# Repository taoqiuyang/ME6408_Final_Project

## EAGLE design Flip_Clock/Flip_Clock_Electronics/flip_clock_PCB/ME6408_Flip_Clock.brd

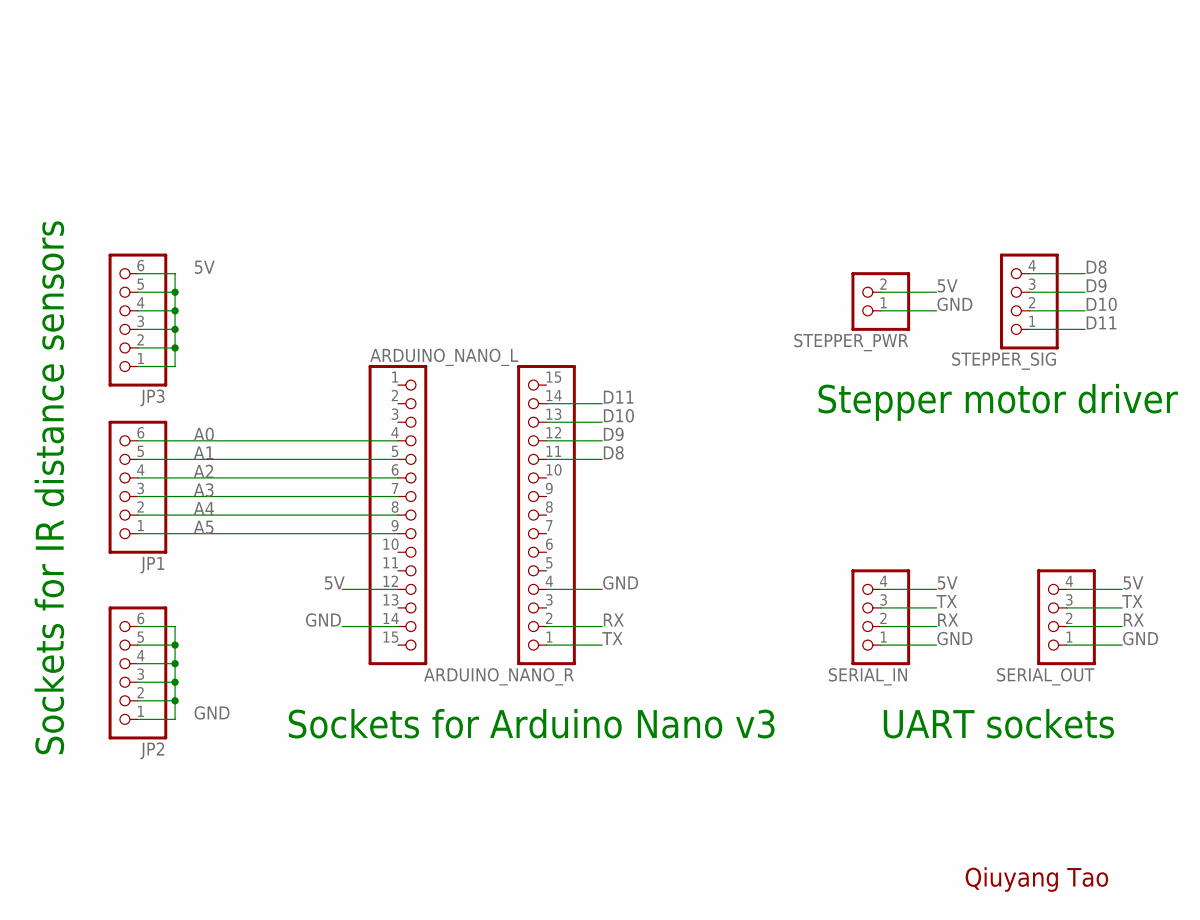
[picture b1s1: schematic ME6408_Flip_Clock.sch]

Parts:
ARDUINO_NANO_L: PINHD-1X15; 1X15
ARDUINO_NANO_R: PINHD-1X15; 1X15
JP1, JP2, JP3: PINHD-1X6; 1X06
SERIAL_IN: PINHD-1X4; 1X04
SERIAL_OUT: PINHD-1X4; 1X04
STEPPER_PWR: PINHD-1X2; 1X02
STEPPER_SIG: PINHD-1X4; 1X04

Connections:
5V: ARDUINO_NANO_L.12, JP3.1, JP3.2, JP3.3, JP3.4, JP3.5, JP3.6, SERIAL_IN.4, SERIAL_OUT.4, STEPPER_PWR.2
A0: ARDUINO_NANO_L.4, JP1.6
A1: ARDUINO_NANO_L.5, JP1.5
A2: ARDUINO_NANO_L.6, JP1.4
A3: ARDUINO_NANO_L.7, JP1.3
A4: ARDUINO_NANO_L.8, JP1.2
A5: ARDUINO_NANO_L.9, JP1.1
D8: ARDUINO_NANO_R.11, STEPPER_SIG.4
D9: ARDUINO_NANO_R.12, STEPPER_SIG.3
D10: ARDUINO_NANO_R.13, STEPPER_SIG.2
D11: ARDUINO_NANO_R.14, STEPPER_SIG.1
GND: ARDUINO_NANO_L.14, ARDUINO_NANO_R.4, JP2.1, JP2.2, JP2.3, JP2.4, JP2.5, JP2.6, SERIAL_IN.1, SERIAL_OUT.1, STEPPER_PWR.1
RX: ARDUINO_NANO_R.2, SERIAL_IN.2, SERIAL_OUT.2
TX: ARDUINO_NANO_R.1, SERIAL_IN.3, SERIAL_OUT.3

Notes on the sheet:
Sockets for Arduino Nano v3
Sockets for IR distance sensors
Stepper motor driver
UART sockets
Qiuyang Tao

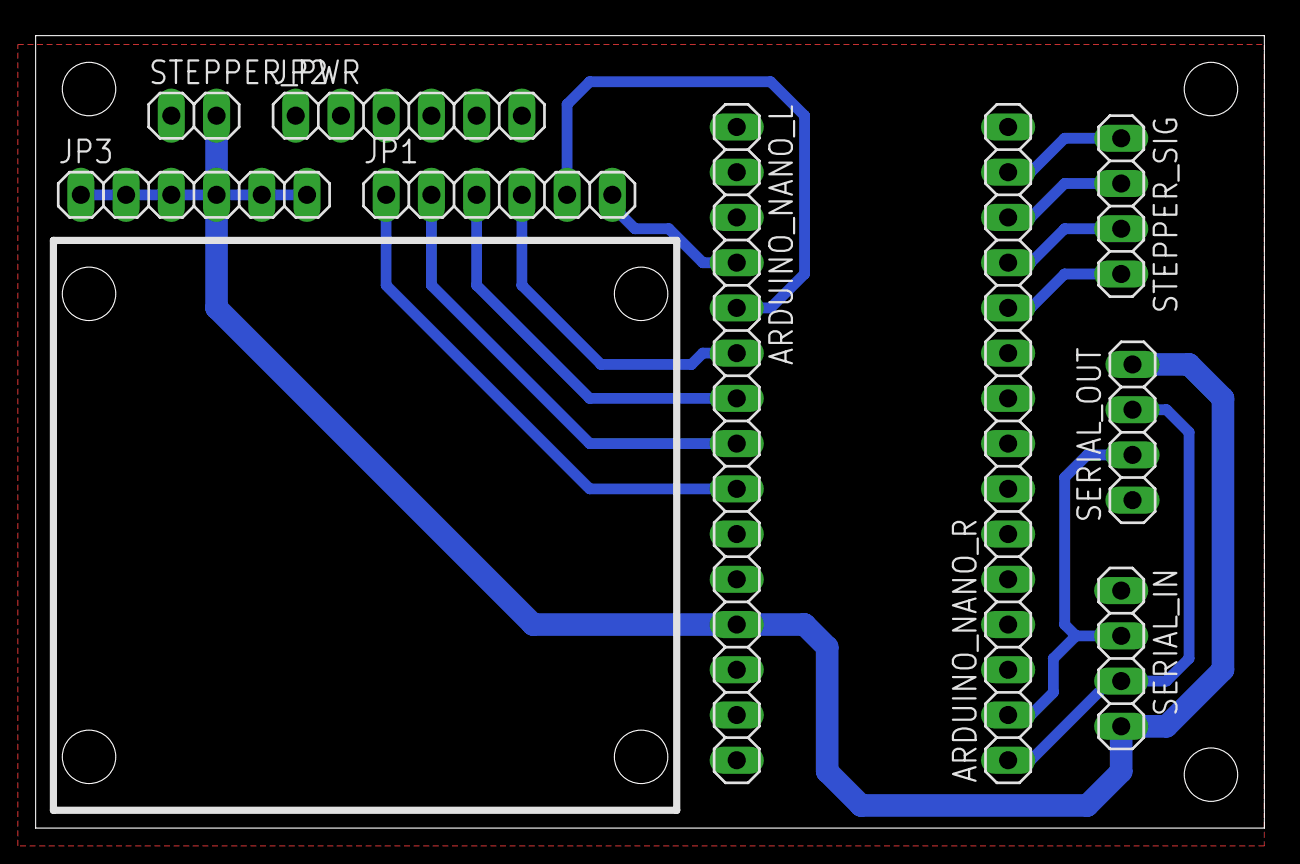
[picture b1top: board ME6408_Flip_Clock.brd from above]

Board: 2 copper layers, 69.0 x 44.5 mm, 9 parts (0 on the bottom side), 14 nets.

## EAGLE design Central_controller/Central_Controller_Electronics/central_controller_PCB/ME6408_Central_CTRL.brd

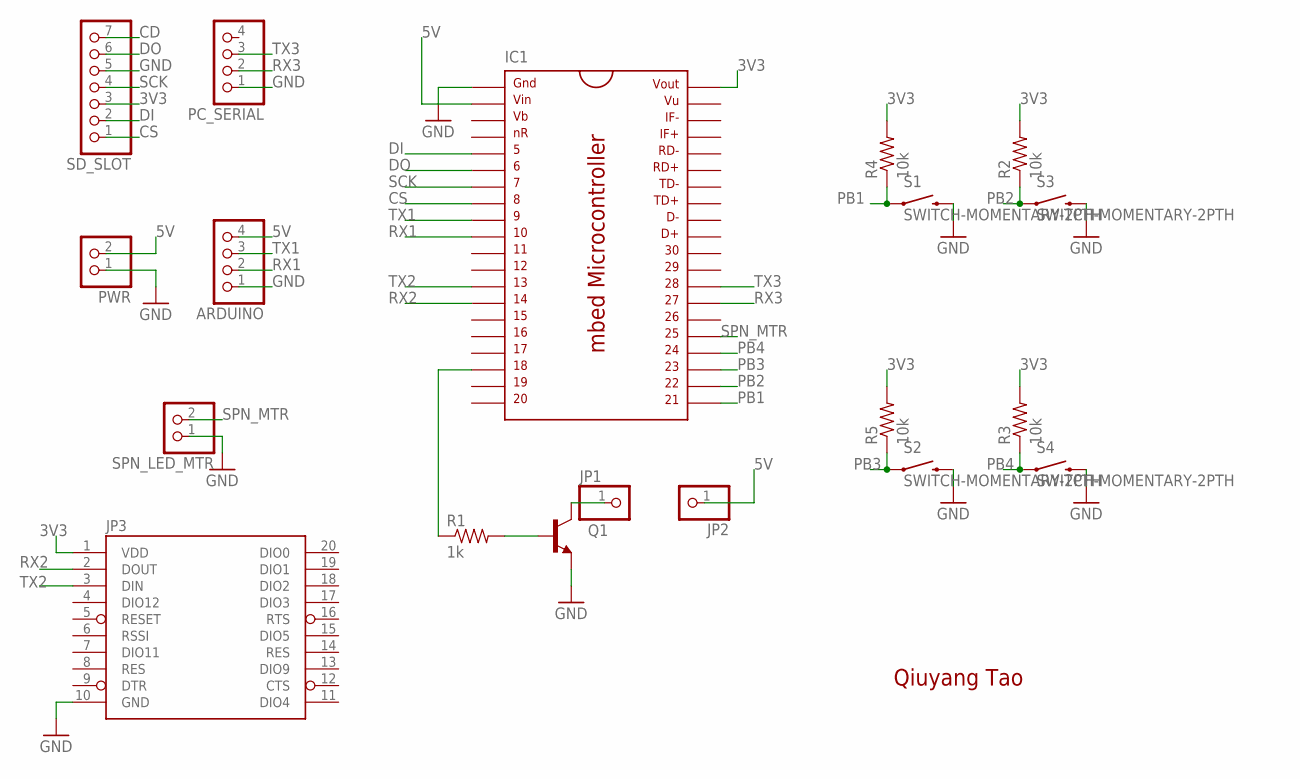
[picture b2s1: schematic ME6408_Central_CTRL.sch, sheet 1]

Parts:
ARDUINO: PINHD-1X4; 1X04
IC1: MBED_MICROCONTROLLER; DIL40_0.9
JP1, JP2: PINHD-1X1; 1X01
JP3: XBEE-1B1; XBEE-1
PC_SERIAL: PINHD-1X4; 1X04
PWR: PINHD-1X2; 1X02
Q1: TRANSISTOR_NPNTO-92-AMMO; TO-92-AMMO
R1: 1k; AXIAL-0.3
R2, R3, R4, R5: 10k; AXIAL-0.3
S1, S2, S3, S4: SWITCH-MOMENTARY-2PTH; TACTILE-PTH
SD_SLOT: PINHD-1X7; 1X07
SPN_LED_MTR: PINHD-1X2; 1X02

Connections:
3V3: IC1.40, JP3.1 (VDD), R2.P$2 (2), R3.P$2 (2), R4.P$2 (2), R5.P$2 (2), SD_SLOT.3
5V: ARDUINO.4, IC1.2, JP2.1, PWR.2
CD: SD_SLOT.7
CS: IC1.8, SD_SLOT.1
DI: IC1.5, SD_SLOT.2
DO: IC1.6, SD_SLOT.6
GND: ARDUINO.1, IC1.1, JP3.10 (GND), PC_SERIAL.1, PWR.1, Q1.1 (E), S1.3 (2), S2.3 (2), S3.3 (2), S4.3 (2), SD_SLOT.5, SPN_LED_MTR.1
unnamed: Q1.2 (B), R1.P$2 (2)
unnamed: JP1.1, Q1.3 (C)
unnamed: IC1.18, R1.P$1 (1)
PB1: IC1.21, R4.P$1 (1), S1.1
PB2: IC1.22, R2.P$1 (1), S3.1
PB3: IC1.23, R5.P$1 (1), S2.1
PB4: IC1.24, R3.P$1 (1), S4.1
RX1: ARDUINO.2, IC1.10
RX2: IC1.14, JP3.2 (DOUT)
RX3: IC1.27, PC_SERIAL.2
SCK: IC1.7, SD_SLOT.4
SPN_MTR: IC1.25, SPN_LED_MTR.2
TX1: ARDUINO.3, IC1.9
TX2: IC1.13, JP3.3 (DIN)
TX3: IC1.28, PC_SERIAL.3

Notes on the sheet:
Qiuyang Tao

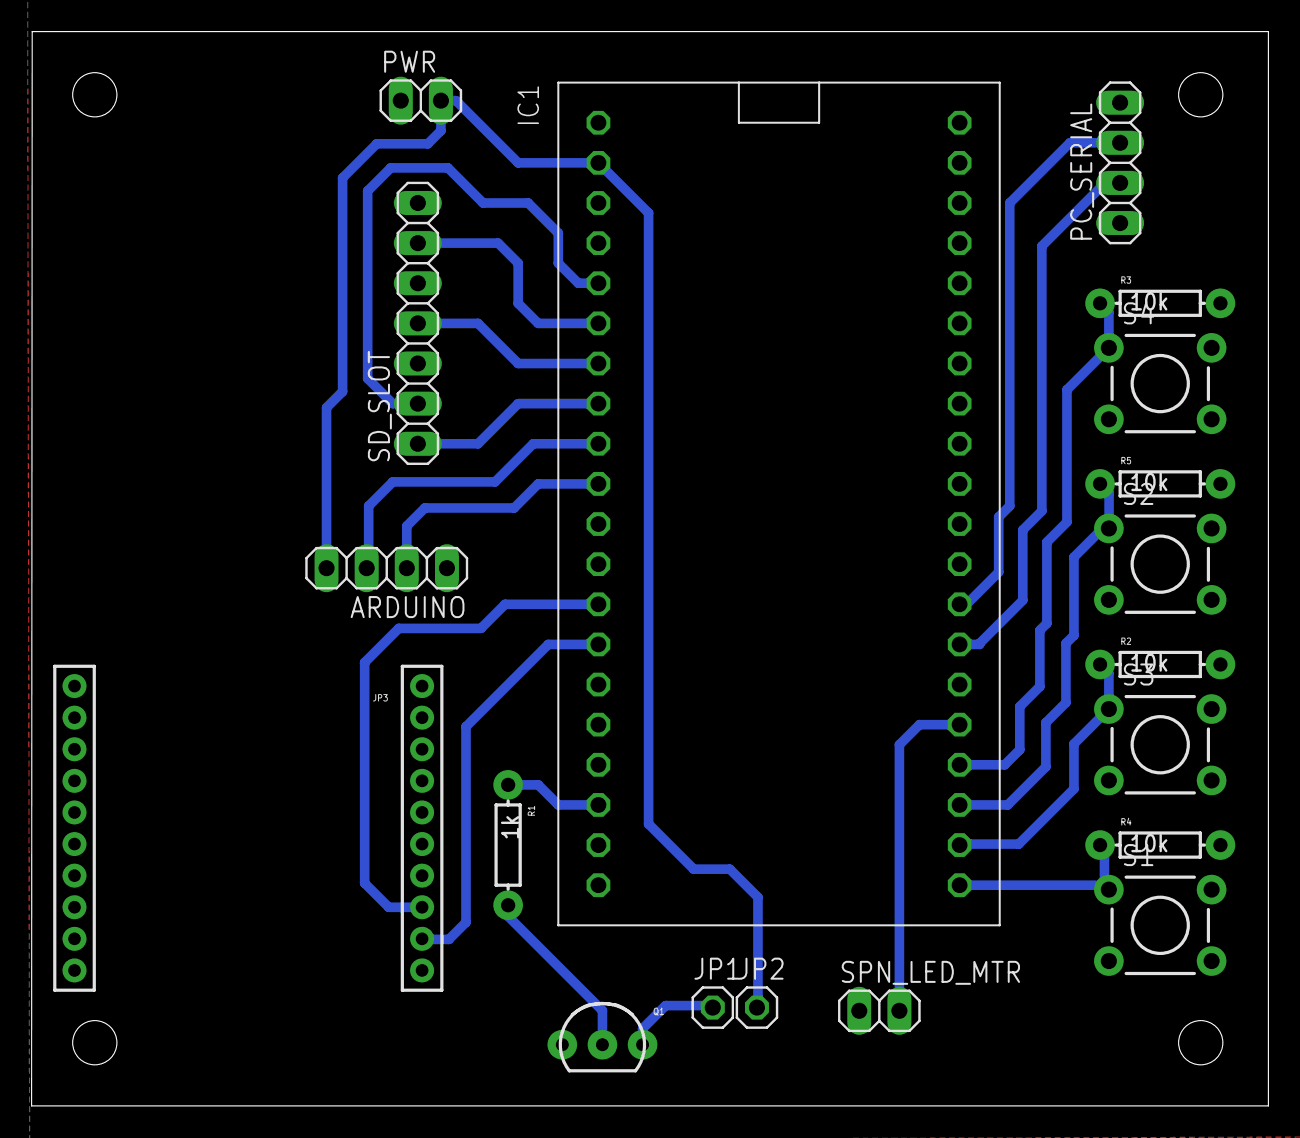
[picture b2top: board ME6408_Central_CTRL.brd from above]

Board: 2 copper layers, 78.3 x 68.0 mm, 19 parts (0 on the bottom side), 21 nets.

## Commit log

2016-04-21 Test upload
2016-04-21 deleted_test_file
2016-04-21 Added files for central controller
2016-04-21 Added files for flip clock
2016-04-21 Added files for POV display
2016-04-21 Added overall system diagram
2016-04-21 Added list of materials

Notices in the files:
parts and their libraries:
SparkFun-DiscreteSemi: Licensing: Creative Commons ShareAlike 4.0 International - https://creativecommons.org/licenses/by-sa/4.0
